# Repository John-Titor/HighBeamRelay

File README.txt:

High-beam switching relay, suitable for low/high 
beam switching with aftermarket Bi-Xenon headlights 
in older VW/Porsche applications.

The unit should be powered from the low-beam light 
power, and the IN pin pulled to ground by the high-beam
switch. The OUT pin should be connected to the positive
terminal of the Bi-Xenon high-beam solenoids.

If the IN pin is pulled briefly to ground, a 250ms flash
followed by a 250ms off period will be generated. If the
pin is held to ground for more than 350ms, the relay will
latch on and remain on until the IN pin is disconnected
from ground and then reconnected.

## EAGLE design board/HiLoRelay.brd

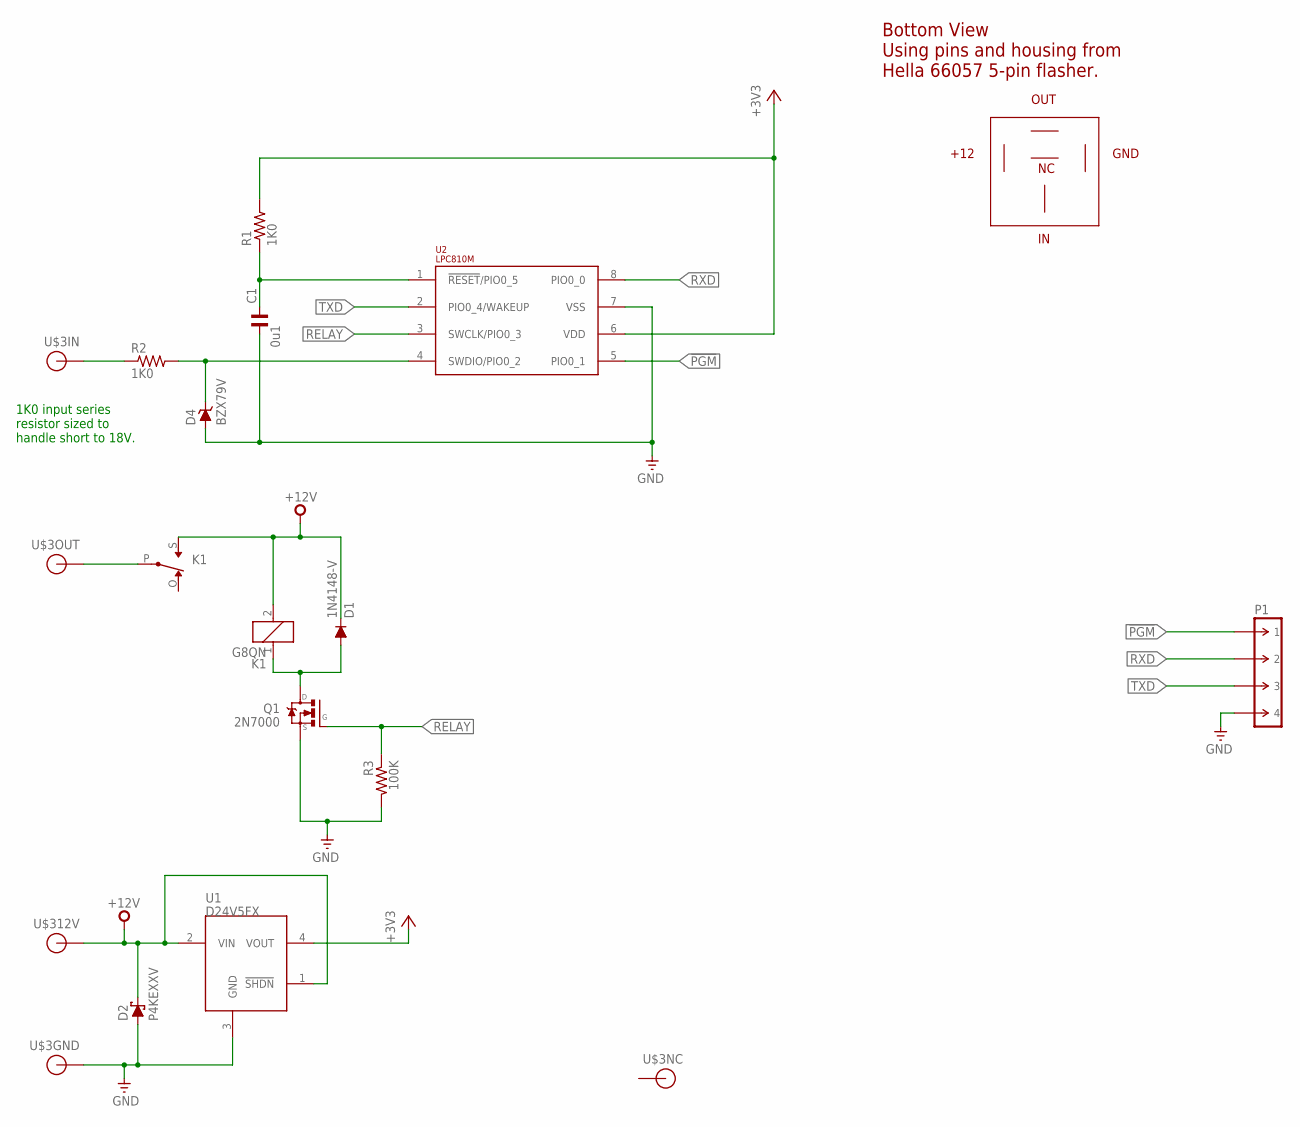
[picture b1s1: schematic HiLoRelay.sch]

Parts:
C1: 0u1; C025-024X044; PARTNO FK18X7R1E104K
D1: 1N4148-V; DO35-V; PARTNO 1N4148
D2: P4KEXXV; DO41-V; PARTNO P4KE30CA
D4: BZX79V; DO35-V; PARTNO TZX3V3A-TR
K1: G8QN; PARTNO G8QN-1C4-DC12
P1: M-1X04-SIP-100-32; SIP-100-04-32; PARTNO 961104-6404-AR
Q1: 2N7000; TO-92; PARTNO 2N7000
R1, R2: 1K0; 0207/2V; PARTNO MFR-25FBF52-1K
R3: 100K; 0207/2V; PARTNO MFR-25FRF52-100K
U1: D24V5FX; SIP-100-04-32
U2: LPC810M; DIL08; PARTNO LPC810M021FN8FP
U$3: TRIDON_PIN_BASE

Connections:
!PGM: P1.1, U2.5 (PIO0_1)
+3V3: R1.2, U1.4 (VOUT), U2.6 (VDD)
+12V: D1.C, D2.C, K1.2, K1.S (NO), U1.1 (!SHDN), U1.2 (VIN), U$3.12V
GND: C1.2, D2.A, D4.A, P1.4, Q1.1 (S), R3.2, U1.3 (GND), U2.7 (VSS), U$3.GND
unnamed: D1.A, K1.1, Q1.3 (D)
unnamed: R2.1, U$3.IN
unnamed: D4.C, R2.2, U2.4 (SWDIO/PIO0_2)
unnamed: C1.1, R1.1, U2.1 (!RESET!/PIO0_5)
OUT: K1.P (COM), U$3.OUT
RELAY: Q1.2 (G), R3.1, U2.3 (SWCLK/PIO0_3)
RXD: P1.2, U2.8 (PIO0_0)
TXD: P1.3, U2.2 (PIO0_4/WAKEUP)

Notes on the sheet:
+12
GND
OUT
Bottom View Using pins and housing from Hella 66057 5-pin flasher.
1K0 input series resistor sized to handle short to 18V.

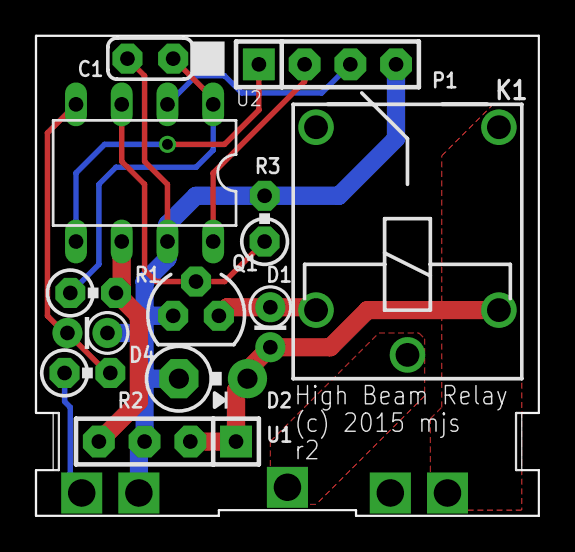
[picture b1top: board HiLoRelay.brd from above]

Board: 2 copper layers, 27.9 x 26.7 mm, 13 parts (0 on the bottom side), 12 nets.

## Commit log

2015-05-26 Initial checkin of the High/Low beam relay design
2015-05-26 Wire up the classlib as a submodule
2015-05-26 Project description

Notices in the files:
board/HiLoRelay.brd:
(c) 2015 mjs
